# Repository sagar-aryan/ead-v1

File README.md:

# EAD V1

A right-leg, barefoot wearable for gait research after stroke, built on error
augmentation. Two IMUs on the foot and shank detect every gait cycle; the device
scores each cycle against the wearer's own recorded baseline and, when a step is off,
cues it through six vibration motors on a calf band. A desktop dashboard records the
raw data, manages baselines and sessions, and exports CSV, MATLAB and PDF.

> Research and engineering prototype. Not a medical device and not a validated clinical
> tool.

*Illustration of the worn layout and motor positions. Exact placement and wiring:
[`docs/hardware.md`](docs/hardware.md), worn assembly.*

## How it works

```text
foot + shank BNO086 (SPI, 200 Hz)
  → XIAO ESP32-S3: orientation, gait events, zero-velocity updates, per-cycle score
  → vibration cue on the device (no laptop in the loop)
  → Wi-Fi access point or USB → dashboard (Tauri): live view, SQLite store, exports
```

- **Gait:** each right-leg cycle is found from the shank's swing; heel strike, toe-off,
  stance, swing, cadence, stride length and speed are computed on the device, with
  foot-flat zero-velocity updates to bound integration drift.
- **Score:** seven features (swing dorsiflexion, contact angle, inversion/eversion,
  cycle time, stance ratio, stride distance, shank swing rate) are compared with the
  baseline's medians and spreads and combined into one score from 0 to 1.
- **Cue:** a score of 0.35 or more starts a 0.5 s buzz, 60–100 % strength by how far off
  the step was. Where it buzzes names the error, on the side to move away from: the
  back of the calf for too little toe lift or a toe-first landing, the inner side for
  rolling onto the outer edge (inversion), the outer side for rolling in (eversion),
  front and back in turn for timing. The buzz stops at the first good step. On-time limits (5 s
  continuous, 50 % over any 10 s) are enforced on the device; sensor faults, a switched
  off feedback toggle, or 5 s without the laptop hold cues back.
- **Data:** every raw sample is kept. A 6 MB buffer on the device holds about 4.5 min,
  so a Wi-Fi dropout is filled in after reconnecting.

## Hardware

| Part | Detail |
|---|---|
| Controller | Seeed XIAO ESP32-S3 (plain, not Sense) |
| IMUs | 2 × 7Semi BNO086 breakout on SPI: foot (dorsum) and shank (anterior shin) |
| Haptics | 6 ERM coin motors around the calf, driven by the PCB in `hardware/erm-driver-pcb/` (tight variant): low-side MOSFETs, two 3.3 V regulators |
| Power | 1S Li-ion cell, charger module, master switch |

Every pin and connection, with its evidence: [`docs/wiring_reference.md`](docs/wiring_reference.md).
All 15 usable XIAO GPIOs are in use.

## Repository

| Folder | Contents |
|---|---|
| `firmware/` | Device firmware (PlatformIO, Arduino-ESP32); portable, host-tested core in `lib/ead_core` |
| `dashboard/` | Desktop app: Rust backend (device link, SQLite, exports) and React frontend |
| `hardware/erm-driver-pcb/` | KiCad project of the motor driver board, with its own docs |
| `protocol/vectors/` | Golden wire-protocol messages and their generator |
| `tools/` | `eadprobe.py` (independent device client), export checkers, walk replay |
| `recordings/` | Walk recordings with counted steps, used to test gait detection |
| `docs/` | Engineering docs: architecture, implementation, hardware, wiring, protocol, handoff |
| `ead_agent_docs_v2/` | The original V1 specification (read-only) |

## Getting started

**Prerequisites:** PlatformIO, Node.js 20+, a stable Rust toolchain, Python 3 with
pyserial (numpy and scipy for the export checker), and on Linux WebKitGTK 4.1.
`scripts/setup-linux.sh check` reports what is missing. Linux is the tested
platform; setup scripts for macOS and Windows are included.

**Firmware:**

```sh
pio run -d firmware -t upload        # build and flash over USB
python3 tools/eadprobe.py hello      # identity, protocol schema, firmware version
python3 tools/eadprobe.py check      # per-wire sensor check
```

The first build creates `firmware/include/ead_secrets.h` with a random Wi-Fi
passphrase. It is ignored by git; never commit it.

**Dashboard:**

```sh
cd dashboard && npm install
npx tauri dev                        # development
npx tauri build --no-bundle          # release build; see dashboard/README.md for `ead`
```

**Connecting:** over USB, or join the device's access point `EAD-V1-xxxx` (passphrase in
`ead_secrets.h`) and connect the dashboard to `ws://192.168.4.1:8080/ws`.

## Using it

1. **Calibrate:** stand still for 5 s with the sensors strapped on.
2. **Baseline:** walk normally on a straight path until at least 30 valid cycles
   (about 60 steps) are collected. Baselines are versioned per patient and locked.
3. **Check:** a short scored walk against the baseline.
4. **Evaluate:** walk with feedback on; the session's limits (cycles, errors) are set
   first.
5. **Export:** raw samples, cycles, events and cues as CSV, plus `metadata.json`,
   `session.mat` and a PDF report.

Calibrate after every restart. A baseline belongs to the strapping it was recorded
in, so record a new one after re-strapping the sensors.

## Testing

```sh
pio test -d firmware -e native                     # firmware core
(cd dashboard/src-tauri && cargo test)             # backend
(cd dashboard && npm test && npm run build)        # frontend
python3 tools/eadprobe.py vectors                  # protocol, against the golden vectors
```

On hardware, `eadprobe stats` and `cargo test hardware -- --ignored --test-threads=1`.

## Safety

- **Never turn the battery switch on while USB is plugged in.** Motor tests run on
  battery over Wi-Fi with USB unplugged.
- Motors are held off from power-up; GPIO39 must never drive a motor
  ([`docs/wiring_reference.md`](docs/wiring_reference.md) §10).

## Status

Working end to end, worn on battery over Wi-Fi: step detection, per-step scoring
against the wearer's own baseline, directional graded cues, and full raw-data export.
Current state and roadmap: [`docs/handoff.md`](docs/handoff.md).

## Documentation

Start with [`docs/handoff.md`](docs/handoff.md); [`docs/README.md`](docs/README.md)
indexes the rest, including the wire protocol ([`docs/protocol.md`](docs/protocol.md)).

## License

MIT ([`LICENSE`](LICENSE)): firmware, dashboard, tools, hardware design files and
documentation. Exceptions keep their own licences: the IBM Plex fonts in
`dashboard/src-tauri/assets/fonts/` (SIL Open Font License 1.1, `OFL.txt` beside them)
and the agent skills in `.claude/skills/` (Apache 2.0 and MIT, as each states). The
software comes with no warranty, and nothing here is cleared for clinical use.

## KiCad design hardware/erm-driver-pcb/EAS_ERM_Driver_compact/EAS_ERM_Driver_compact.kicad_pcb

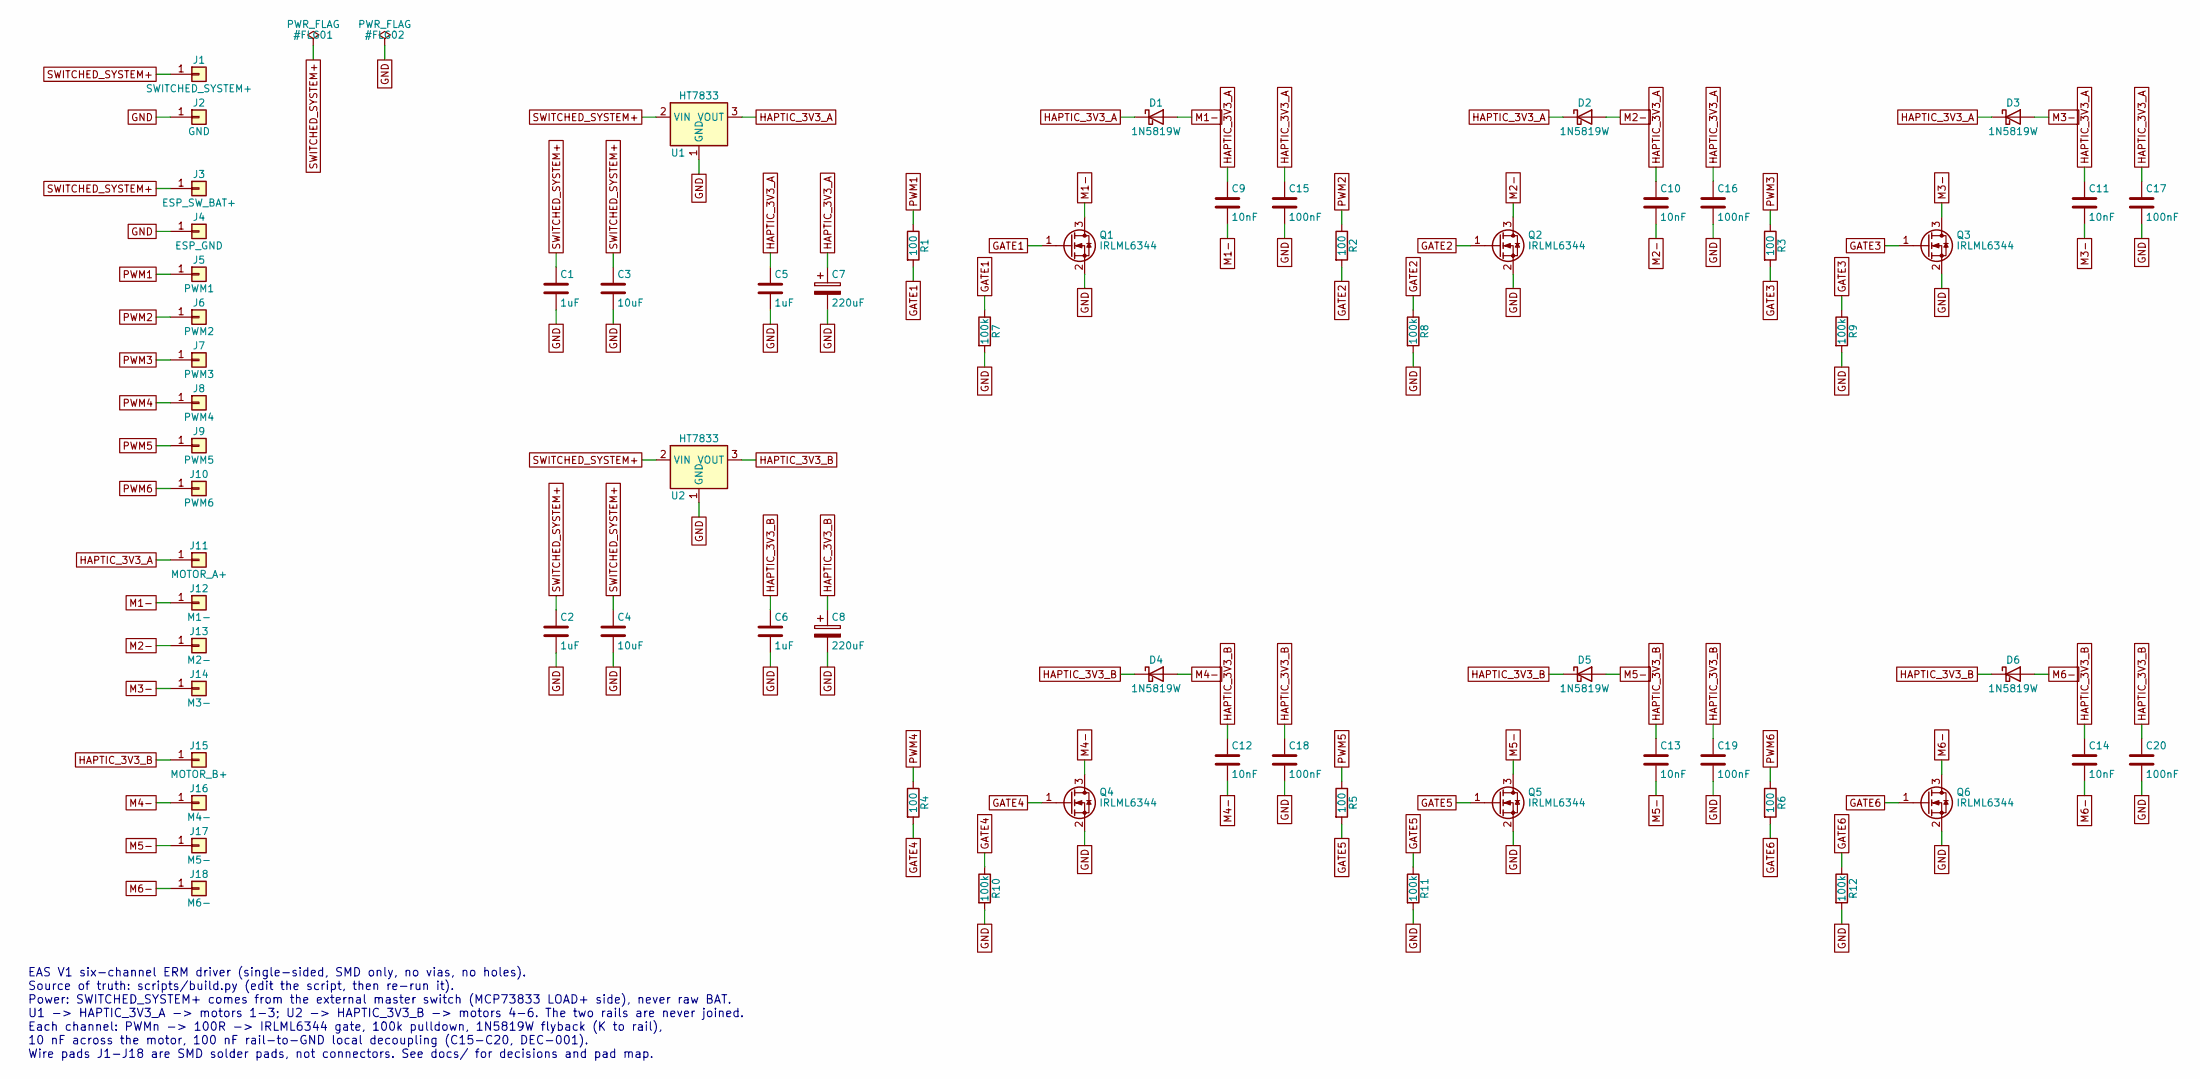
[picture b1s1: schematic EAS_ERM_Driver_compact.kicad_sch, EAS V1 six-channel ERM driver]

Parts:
C1, C2, C5, C6: 1uF; C_1206_3216Metric_Pad1.33x1.80mm_HandSolder
C3, C4: 10uF; C_1206_3216Metric_Pad1.33x1.80mm_HandSolder
C7, C8: 220uF; CP_Elec_5x5.9
C9, C10, C11, C12, C13, C14: 10nF; C_1206_3216Metric_Pad1.33x1.80mm_HandSolder
C15, C16, C17, C18, C19, C20: 100nF; C_1206_3216Metric_Pad1.33x1.80mm_HandSolder
D1, D2, D3, D4, D5, D6: 1N5819W; D_SOD-123
J1: SWITCHED_SYSTEM+; WirePad_3.0x2.5mm
J2: GND; WirePad_3.0x2.5mm
J3: ESP_SW_BAT+; WirePad_2.0x2.0mm
J4: ESP_GND; WirePad_2.0x2.0mm
J5: PWM1; WirePad_2.0x2.0mm
J6: PWM2; WirePad_2.0x2.0mm
J7: PWM3; WirePad_2.0x2.0mm
J8: PWM4; WirePad_2.0x2.0mm
J9: PWM5; WirePad_2.0x2.0mm
J10: PWM6; WirePad_2.0x2.0mm
J11: MOTOR_A+; WirePad_2.5x7.0mm
J12: M1-; WirePad_2.5x2.5mm
J13: M2-; WirePad_2.5x2.5mm
J14: M3-; WirePad_2.5x2.5mm
J15: MOTOR_B+; WirePad_2.5x7.0mm
J16: M4-; WirePad_2.5x2.5mm
J17: M5-; WirePad_2.5x2.5mm
J18: M6-; WirePad_2.5x2.5mm
Q1, Q2, Q3, Q4, Q5, Q6: IRLML6344; SOT-23_Handsoldering
R1, R2, R3, R4, R5, R6: 100; R_1206_3216Metric_Pad1.30x1.75mm_HandSolder
R7, R8, R9, R10, R11, R12: 100k; R_1206_3216Metric_Pad1.30x1.75mm_HandSolder
U1, U2: HT7833; SOT-89-3_Handsoldering_0.4mm

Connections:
GATE1: Q1.1 (G), R1.2, R7.1
GATE2: Q2.1 (G), R2.2, R8.1
GATE3: Q3.1 (G), R3.2, R9.1
GATE4: Q4.1 (G), R4.2, R10.1
GATE5: Q5.1 (G), R5.2, R11.1
GATE6: Q6.1 (G), R6.2, R12.1
GND: C1.2, C2.2, C3.2, C4.2, C5.2, C6.2, C7.2, C8.2, C15.2, C16.2, C17.2, C18.2, C19.2, C20.2, J2.1, J4.1, Q1.2 (S), Q2.2 (S), Q3.2 (S), Q4.2 (S), Q5.2 (S), Q6.2 (S), R7.2, R8.2, R9.2, R10.2, R11.2, R12.2, U1.1 (GND), U2.1 (GND)
HAPTIC_3V3_A: C5.1, C7.1, C9.1, C10.1, C11.1, C15.1, C16.1, C17.1, D1.1 (K), D2.1 (K), D3.1 (K), J11.1, U1.3 (VOUT)
HAPTIC_3V3_B: C6.1, C8.1, C12.1, C13.1, C14.1, C18.1, C19.1, C20.1, D4.1 (K), D5.1 (K), D6.1 (K), J15.1, U2.3 (VOUT)
M1-: C9.2, D1.2 (A), J12.1, Q1.3 (D)
M2-: C10.2, D2.2 (A), J13.1, Q2.3 (D)
M3-: C11.2, D3.2 (A), J14.1, Q3.3 (D)
M4-: C12.2, D4.2 (A), J16.1, Q4.3 (D)
M5-: C13.2, D5.2 (A), J17.1, Q5.3 (D)
M6-: C14.2, D6.2 (A), J18.1, Q6.3 (D)
PWM1: J5.1, R1.1
PWM2: J6.1, R2.1
PWM3: J7.1, R3.1
PWM4: J8.1, R4.1
PWM5: J9.1, R5.1
PWM6: J10.1, R6.1
SWITCHED_SYSTEM+: C1.1, C2.1, C3.1, C4.1, J1.1, J3.1, U1.2 (VIN), U2.2 (VIN)

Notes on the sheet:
EAS V1 six-channel ERM driver (single-sided, SMD only, no vias, no holes). Source of truth: scripts/build.py (edit the script, then re-run it). Power: SWITCHED_SYSTEM+ comes from the external master switch (MCP73833 LOAD+ side), never raw BAT. U1 -> HAPTIC_3V3_A -> motors 1-3; U2 -> HAPTIC_3V3_B ->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

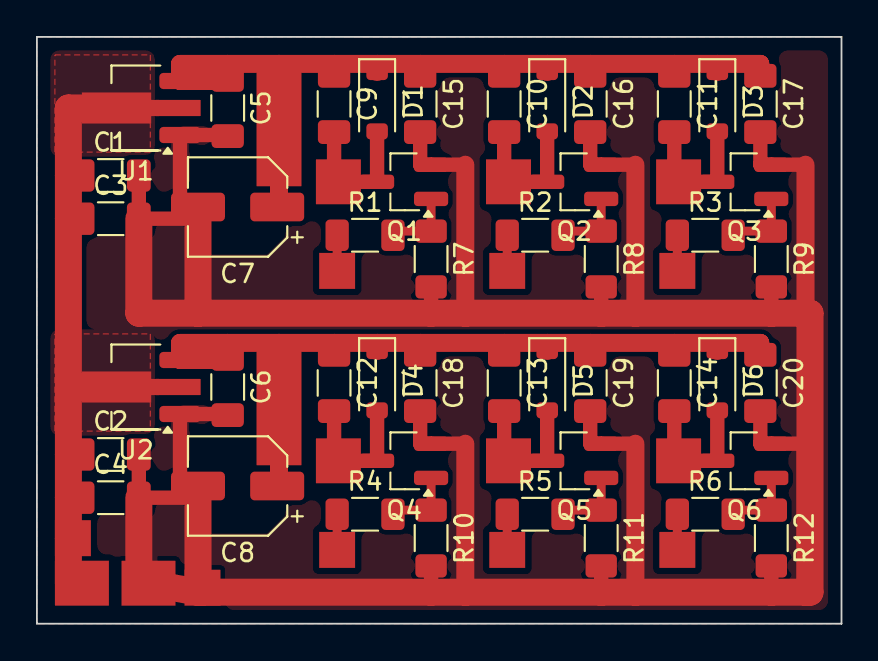
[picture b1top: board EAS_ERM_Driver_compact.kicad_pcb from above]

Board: 2 copper layers, 44.7 x 32.6 mm, 64 parts (0 on the bottom side), 22 nets.

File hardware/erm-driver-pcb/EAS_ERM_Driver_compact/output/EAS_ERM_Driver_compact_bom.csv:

"Refs","Value","Footprint","Description","Qty"
"C1,C2,C5,C6","1uF","Capacitor_SMD:C_1206_3216Metric_Pad1.33x1.80mm_HandSolder","U1 input, X7R 50 V,U1 output, X7R 50 V,U2 input, X7R 50 V,U2 output, X7R 50 V","4"
"C3,C4","10uF","Capacitor_SMD:C_1206_3216Metric_Pad1.33x1.80mm_HandSolder","U1 input bulk, X7R,U2 input bulk, X7R","2"
"C7,C8","220uF","Capacitor_SMD:CP_Elec_5x5.9","Rail A bulk, 6.3 V polymer, SMD V-chip D5,Rail B bulk, 6.3 V polymer, SMD V-chip D5","2"
"C9-C14","10nF","Capacitor_SMD:C_1206_3216Metric_Pad1.33x1.80mm_HandSolder","Motor 1 suppression, across motor,Motor 2 suppression, across motor,Motor 3 suppression, across motor,Motor 4 suppression, across motor,Motor 5 suppression, across motor,Motor 6 suppression, across motor","6"
"C15-C20","100nF","Capacitor_SMD:C_1206_3216Metric_Pad1.33x1.80mm_HandSolder","Channel 1 local rail decoupling (DEC-001),Channel 2 local rail decoupling (DEC-001),Channel 3 local rail decoupling (DEC-001),Channel 4 local rail decoupling (DEC-001),Channel 5 local rail decoupling (DEC-001),Channel 6 local rail decoupling (DEC-001)","6"
"D1-D6","1N5819W","Diode_SMD:D_SOD-123","Flyback, motor 1,Flyback, motor 2,Flyback, motor 3,Flyback, motor 4,Flyback, motor 5,Flyback, motor 6","6"
"J1","SWITCHED_SYSTEM+","EAS:WirePad_3.0x2.5mm","SMD wire solder pad (no hole)","1"
"J2","GND","EAS:WirePad_3.0x2.5mm","SMD wire solder pad (no hole)","1"
"J3","ESP_SW_BAT+","EAS:WirePad_2.0x2.0mm","SMD wire solder pad (no hole)","1"
"J4","ESP_GND","EAS:WirePad_2.0x2.0mm","SMD wire solder pad (no hole)","1"
"J5","PWM1","EAS:WirePad_2.0x2.0mm","SMD wire solder pad (no hole)","1"
"J6","PWM2","EAS:WirePad_2.0x2.0mm","SMD wire solder pad (no hole)","1"
"J7","PWM3","EAS:WirePad_2.0x2.0mm","SMD wire solder pad (no hole)","1"
"J8","PWM4","EAS:WirePad_2.0x2.0mm","SMD wire solder pad (no hole)","1"
"J9","PWM5","EAS:WirePad_2.0x2.0mm","SMD wire solder pad (no hole)","1"
"J10","PWM6","EAS:WirePad_2.0x2.0mm","SMD wire solder pad (no hole)","1"
"J11","MOTOR_A+","EAS:WirePad_2.5x7.0mm","SMD wire solder pad (no hole)","1"
"J12","M1-","EAS:WirePad_2.5x2.5mm","SMD wire solder pad (no hole)","1"
"J13","M2-","EAS:WirePad_2.5x2.5mm","SMD wire solder pad (no hole)","1"
"J14","M3-","EAS:WirePad_2.5x2.5mm","SMD wire solder pad (no hole)","1"
"J15","MOTOR_B+","EAS:WirePad_2.5x7.0mm","SMD wire solder pad (no hole)","1"
"J16","M4-","EAS:WirePad_2.5x2.5mm","SMD wire solder pad (no hole)","1"
"J17","M5-","EAS:WirePad_2.5x2.5mm","SMD wire solder pad (no hole)","1"
"J18","M6-","EAS:WirePad_2.5x2.5mm","SMD wire solder pad (no hole)","1"
"Q1-Q6","IRLML6344","Package_TO_SOT_SMD:SOT-23_Handsoldering","Low-side switch, motor 1,Low-side switch, motor 2,Low-side switch, motor 3,Low-side switch, motor 4,Low-side switch, motor 5,Low-side switch, motor 6","6"
"R1-R6","100","Resistor_SMD:R_1206_3216Metric_Pad1.30x1.75mm_HandSolder","Gate series, channel 1,Gate series, channel 2,Gate series, channel 3,Gate series, channel 4,Gate series, channel 5,Gate series, channel 6","6"
"R7-R12","100k","Resistor_SMD:R_1206_3216Metric_Pad1.30x1.75mm_HandSolder","Gate pulldown, channel 1,Gate pulldown, channel 2,Gate pulldown, channel 3,Gate pulldown, channel 4,Gate pulldown, channel 5,Gate pulldown, channel 6","6"
"U1,U2","HT7833","EAS:SOT-89-3_Handsoldering_0.4mm","3.3 V LDO, rail A (M1-M3),3.3 V LDO, rail B (M4-M6)","2"
